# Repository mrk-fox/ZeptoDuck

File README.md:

<div align="center">
<h1>ZeptoDuck</h1><br>
The smallest "Rubber Ducky" in the world.
<br>

<br>

</div>

# What is ZeptoDuck about?
In the world of rising digital vurneablility due to the effects of digitalization we are forced to develop tools to pentest the security structures we have developed and established over the years. One poular tool attackers use is the "Rubber Ducky". It is a broad term for a programmable HID execution device. The ZeptoDuck project, with the term "Zepto" coming from the greek word ζεπτο meaning one sextilionth is a electronics project to build such a device. The term "Zepto" was used to display the size of the ZeptoDuck being only about 10x3x15mm. This would be the world record for the smallest rubber ducky ever produced. 

# Features
ZeptoDuck covers a narrow spectre of features dur to its very specific usecase.

- ATSAMD11D14A-UUT as the main MCU
- Programmable via the SWD pads and the USB-C port with correct software.
- HID Input device capabilities.

# PCB and Schematics

The PCB itself is a minatuarized 2-Layer FR4 PCB with only a few components, most of them in very small formats.

# Assembly and Flashing

1. Apply solder paste through the soldermask on all necessary components footprints
2. Place the components on the PCB
3. Use a hotplate to solder the components to the PCB
4. Cut off the additional holders for the USB-C port
5. Flip the PCB and hand-solder the USB-C port (The hard part)
6. Flash the PCB using any pogo pin assembly while applying 5V voltage through the USB-C port
7. Youre ready to hack!

# BOM

| id | Name                          | Qty | Price |   |
|----|-------------------------------|-----|-------|---|
| 1  | PCB                           | 1   | 11.5$ |   |
| 2  | ATSAMD11D14A-UUT              | 10  | 16$   |   |
| 3  | TLV73333PDQNR                 | 10  | 5$    |   |
| 4  | WWE Shipping and Handling     | 4   | 39$   |   |
| x  | All other parts are in stock. | x   | x     |   |
| x  | TOTAL                         |     | 71.5$ |   |

# Information for reviewers
28.08.2026: The parts are avalible via a custom agreement between me and Worldway electronics. This project required 22 hours in total to finish. Thanks for reviewing.

# Thanks
I generously thank Worldway Electronics for kindy agreeing on an MOQ relaxation. <br>

Make sure to check out their website! 
worldwayelec.com

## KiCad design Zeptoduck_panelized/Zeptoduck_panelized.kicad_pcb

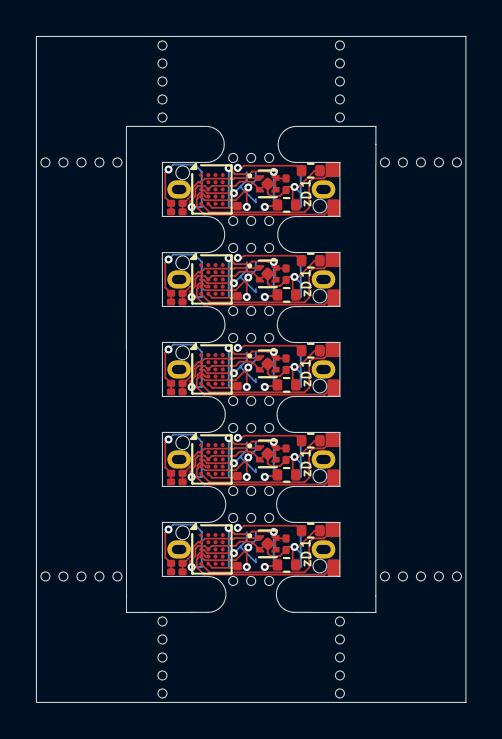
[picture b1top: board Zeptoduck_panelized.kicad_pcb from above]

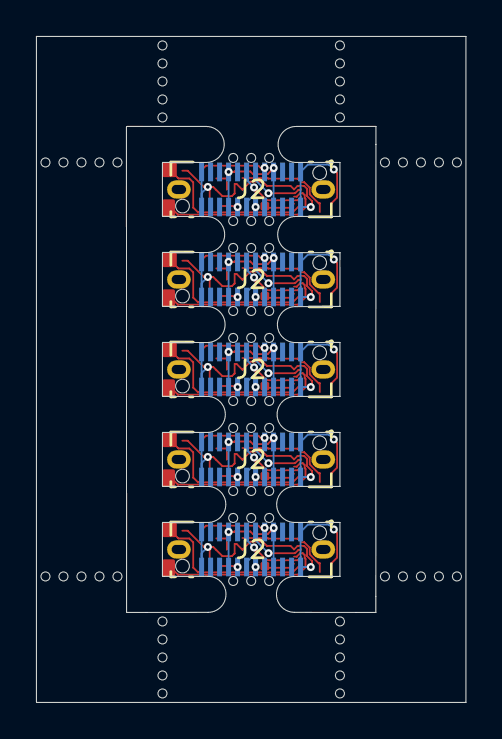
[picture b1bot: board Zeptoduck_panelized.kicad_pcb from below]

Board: 2 copper layers, 23.9 x 37.0 mm, 110 parts (5 on the bottom side), 35 nets.

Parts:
C1, C1#2, C1#3, C1#4, C1#5: 100nF; C_0201_0603Metric
C2, C2#2, C2#3, C2#4, C2#5, C3, C3#2, C3#3, C3#4, C3#5: 1µF; C_0201_0603Metric
J2, J2#2, J2#3, J2#4, J2#5: USB4151-GF-C; USB4151-GF-C_GCT_LESS
KiKit_MB_1_2, KiKit_MB_1_3, KiKit_MB_1_4, KiKit_MB_2_2, KiKit_MB_2_3, KiKit_MB_2_4, KiKit_MB_3_2, KiKit_MB_3_3, KiKit_MB_3_4, KiKit_MB_4_2, KiKit_MB_4_3, KiKit_MB_4_4, KiKit_MB_5_2, KiKit_MB_5_3, KiKit_MB_5_4, KiKit_MB_6_2, KiKit_MB_6_3, KiKit_MB_6_4, KiKit_MB_7_2, KiKit_MB_7_3, KiKit_MB_7_4, KiKit_MB_8_2, KiKit_MB_8_3, KiKit_MB_8_4, KiKit_MB_9_2, KiKit_MB_9_3, KiKit_MB_9_4, KiKit_MB_10_2, KiKit_MB_10_3, KiKit_MB_10_4, KiKit_MB_11_2, KiKit_MB_11_3, KiKit_MB_11_4, KiKit_MB_11_5, KiKit_MB_11_6, KiKit_MB_12_2, KiKit_MB_12_3, KiKit_MB_12_4, KiKit_MB_12_5, KiKit_MB_12_6, KiKit_MB_13_2, KiKit_MB_13_3, KiKit_MB_13_4, KiKit_MB_13_5, KiKit_MB_13_6, KiKit_MB_14_2, KiKit_MB_14_3, KiKit_MB_14_4, KiKit_MB_14_5, KiKit_MB_14_6, KiKit_MB_15_2, KiKit_MB_15_3, KiKit_MB_15_4, KiKit_MB_15_5, KiKit_MB_15_6, KiKit_MB_16_2, KiKit_MB_16_3, KiKit_MB_16_4, KiKit_MB_16_5, KiKit_MB_16_6, KiKit_MB_17_2, KiKit_MB_17_3, KiKit_MB_17_4, KiKit_MB_17_5, KiKit_MB_17_6, KiKit_MB_18_2, KiKit_MB_18_3, KiKit_MB_18_4, KiKit_MB_18_5, KiKit_MB_18_6: NPTH
R1, R1#2, R1#3, R1#4, R1#5, R2, R2#2, R2#3, R2#4, R2#5: 5.1k; R_0402_1005Metric
U1, U1#2, U1#3, U1#4, U1#5: ATSAMD11D14A-U; WLCSP-20_1.934x2.434mm_Layout4x5_P0.4mm
U2, U2#2, U2#3, U2#4, U2#5: TLV73333PDQNR; Texas_X2SON-4_1x1mm_P0.65mm

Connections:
Board_0-/USB_D_M: J2#3.A7 (DN1), J2#3.B7 (DN2), U1#5.D1 (PA24)
Board_0-/USB_D_P: J2#3.A6 (DP1), J2#3.B6 (DP2), U1#5.C1 (PA25)
Board_0-/VBUS: C2#2.2, J2#3.A4 (VBUS), J2#3.A9 (VBUS), J2#3.B4 (VBUS), J2#3.B9 (VBUS), U2#3.3 (EN), U2#3.4 (IN)
Board_0-/VDD: C1#4.2, C3#4.2, U1#5.B1 (VDD), U2#3.1 (OUT)
Board_0-GND: C1#4.1, C2#2.1, C3#4.1, J2#3.A1 (GND), J2#3.A12 (GND), J2#3.B1 (GND), J2#3.B12 (GND), R1#4.2, R2#3.2, U1#5.C2 (GND), U2#3.2 (GND), U2#3.5 (THV)
Board_0-Net-(J2-CC1): J2#3.A5 (CC1), R2#3.1
Board_0-Net-(J2-CC2): J2#3.B5 (CC2), R1#4.1
Board_1-/USB_D_M: J2#4.A7 (DN1), J2#4.B7 (DN2), U1#4.D1 (PA24)
Board_1-/USB_D_P: J2#4.A6 (DP1), J2#4.B6 (DP2), U1#4.C1 (PA25)
Board_1-/VBUS: C2#3.2, J2#4.A4 (VBUS), J2#4.A9 (VBUS), J2#4.B4 (VBUS), J2#4.B9 (VBUS), U2#4.3 (EN), U2#4.4 (IN)
Board_1-/VDD: C1#5.2, C3#2.2, U1#4.B1 (VDD), U2#4.1 (OUT)
Board_1-GND: C1#5.1, C2#3.1, C3#2.1, J2#4.A1 (GND), J2#4.A12 (GND), J2#4.B1 (GND), J2#4.B12 (GND), R1#2.2, R2#5.2, U1#4.C2 (GND), U2#4.2 (GND), U2#4.5 (THV)
Board_1-Net-(J2-CC1): J2#4.A5 (CC1), R2#5.1
Board_1-Net-(J2-CC2): J2#4.B5 (CC2), R1#2.1
Board_2-/USB_D_M: J2#2.A7 (DN1), J2#2.B7 (DN2), U1#3.D1 (PA24)
Board_2-/USB_D_P: J2#2.A6 (DP1), J2#2.B6 (DP2), U1#3.C1 (PA25)
Board_2-/VBUS: C2#5.2, J2#2.A4 (VBUS), J2#2.A9 (VBUS), J2#2.B4 (VBUS), J2#2.B9 (VBUS), U2#5.3 (EN), U2#5.4 (IN)
Board_2-/VDD: C1#2.2, C3.2, U1#3.B1 (VDD), U2#5.1 (OUT)
Board_2-GND: C1#2.1, C2#5.1, C3.1, J2#2.A1 (GND), J2#2.A12 (GND), J2#2.B1 (GND), J2#2.B12 (GND), R1.2, R2.2, U1#3.C2 (GND), U2#5.2 (GND), U2#5.5 (THV)
Board_2-Net-(J2-CC1): J2#2.A5 (CC1), R2.1
Board_2-Net-(J2-CC2): J2#2.B5 (CC2), R1.1
Board_3-/USB_D_M: J2#5.A7 (DN1), J2#5.B7 (DN2), U1#2.D1 (PA24)
Board_3-/USB_D_P: J2#5.A6 (DP1), J2#5.B6 (DP2), U1#2.C1 (PA25)
Board_3-/VBUS: C2#4.2, J2#5.A4 (VBUS), J2#5.A9 (VBUS), J2#5.B4 (VBUS), J2#5.B9 (VBUS), U2.3 (EN), U2.4 (IN)
Board_3-/VDD: C1.2, C3#5.2, U1#2.B1 (VDD), U2.1 (OUT)
Board_3-GND: C1.1, C2#4.1, C3#5.1, J2#5.A1 (GND), J2#5.A12 (GND), J2#5.B1 (GND), J2#5.B12 (GND), R1#5.2, R2#4.2, U1#2.C2 (GND), U2.2 (GND), U2.5 (THV)
Board_3-Net-(J2-CC1): J2#5.A5 (CC1), R2#4.1
Board_3-Net-(J2-CC2): J2#5.B5 (CC2), R1#5.1
Board_4-/USB_D_M: J2.A7 (DN1), J2.B7 (DN2), U1.D1 (PA24)
Board_4-/USB_D_P: J2.A6 (DP1), J2.B6 (DP2), U1.C1 (PA25)
Board_4-/VBUS: C2.2, J2.A4 (VBUS), J2.A9 (VBUS), J2.B4 (VBUS), J2.B9 (VBUS), U2#2.3 (EN), U2#2.4 (IN)
Board_4-/VDD: C1#3.2, C3#3.2, U1.B1 (VDD), U2#2.1 (OUT)
Board_4-GND: C1#3.1, C2.1, C3#3.1, J2.A1 (GND), J2.A12 (GND), J2.B1 (GND), J2.B12 (GND), R1#3.2, R2#2.2, U1.C2 (GND), U2#2.2 (GND), U2#2.5 (THV)
Board_4-Net-(J2-CC1): J2.A5 (CC1), R2#2.1
Board_4-Net-(J2-CC2): J2.B5 (CC2), R1#3.1

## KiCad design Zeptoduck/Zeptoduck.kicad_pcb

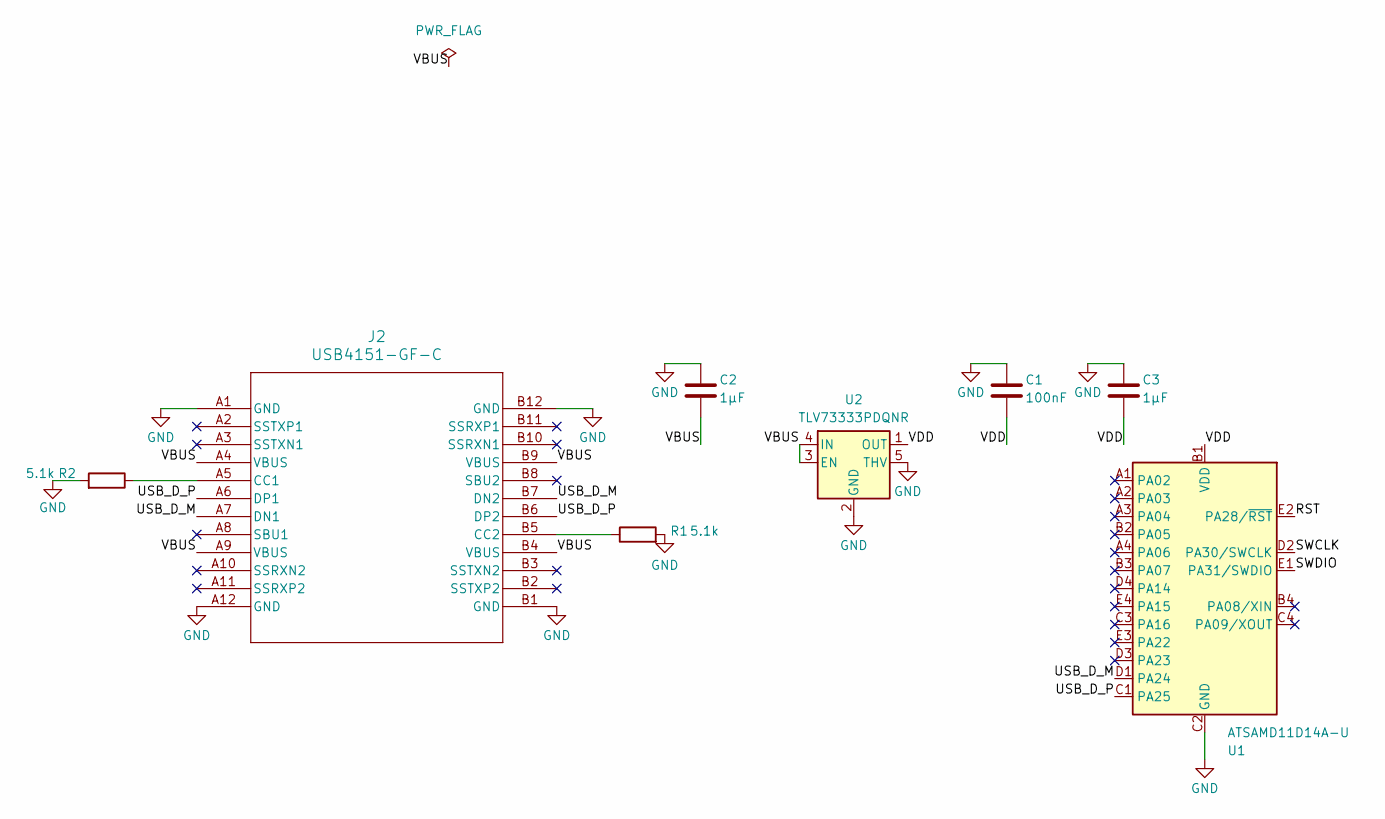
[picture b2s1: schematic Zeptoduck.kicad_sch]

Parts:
C1: 100nF; C_0201_0603Metric
C2, C3: 1µF; C_0201_0603Metric
J2: USB4151-GF-C; USB4151-GF-C_GCT_LESS
R1, R2: 5.1k; R_0402_1005Metric
U1: ATSAMD11D14A-U; WLCSP-20_1.934x2.434mm_Layout4x5_P0.4mm
U2: TLV73333PDQNR; Texas_X2SON-4_1x1mm_P0.65mm

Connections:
/RST: U1.E2 (PA28/~RST)
/SWCLK: U1.D2 (PA30/SWCLK)
/SWDIO: U1.E1 (PA31/SWDIO)
/USB_D_M: J2.A7 (DN1), J2.B7 (DN2), U1.D1 (PA24)
/USB_D_P: J2.A6 (DP1), J2.B6 (DP2), U1.C1 (PA25)
/VBUS: C2.2, J2.A4 (VBUS), J2.A9 (VBUS), J2.B4 (VBUS), J2.B9 (VBUS), U2.3 (EN), U2.4 (IN)
/VDD: C1.2, C3.2, U1.B1 (VDD), U2.1 (OUT)
GND: C1.1, C2.1, C3.1, J2.A1 (GND), J2.A12 (GND), J2.B1 (GND), J2.B12 (GND), R1.2, R2.2, U1.C2 (GND), U2.2 (GND), U2.5 (THV)
unnamed: J2.A5 (CC1), R2.1
unnamed: J2.B5 (CC2), R1.1

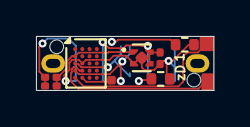
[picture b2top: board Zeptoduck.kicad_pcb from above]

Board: 2 copper layers, 9.9 x 3.0 mm, 8 parts (1 on the bottom side), 7 nets.

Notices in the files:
README.md:
License: CERN-OHL-S
